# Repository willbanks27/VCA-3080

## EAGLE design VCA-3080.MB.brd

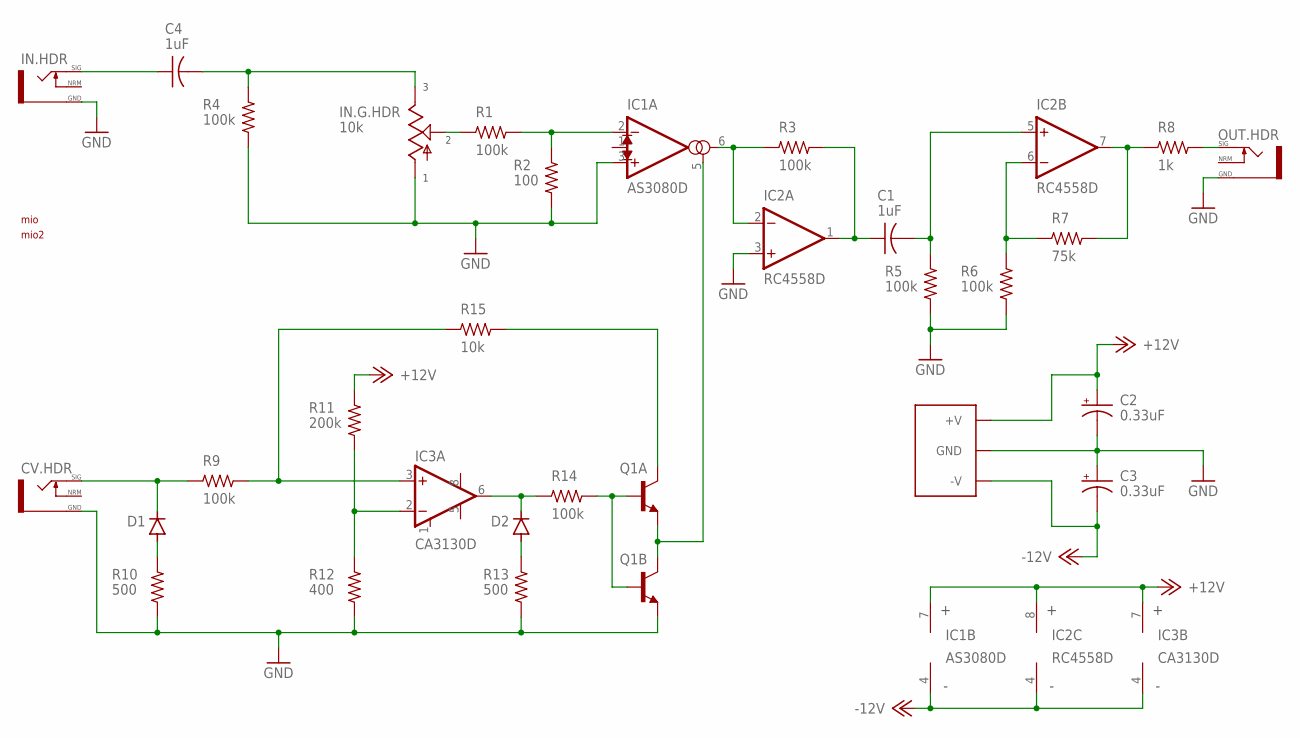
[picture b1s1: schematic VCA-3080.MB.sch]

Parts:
C1, C4: 1uF; C05
C2, C3: 0.33uF; E025
CV.HDR: MONOHDR; HEADER
D1, D2: D-123; SOD-123
IC1: AS3080D; DIL08
IC2: RC4558D; DIL08
IC3: CA3130D; DIL08
IN.G.HDR: 10k; HEADER
IN.HDR: MONOHDR; HEADER
OUT.HDR: MONOHDR; HEADER
Q1: BCM847DS; SOT-23-6
R1, R3, R4, R5, R6, R9, R14: 100k; R1206
R2: 100; R1206
R7: 75k; R1206
R8: 1k; R1206
R10, R13: 500; R1206
R11: 200k; R1206
R12: 400; R1206
R15: 10k; R1206
U$1: 10PIN-PWR; 10PIN-HEADER
U$2: MIO
U$3: MIO2

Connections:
+12V: C2.+, IC1.7 (V+), IC2.8 (V+), IC3.7 (V+), R11.2, U$1.9 (+V), U$1.10 (+V)
-12V: C3.-, IC1.4 (V-), IC2.4 (V-), IC3.4 (V-), U$1.1 (-V), U$1.2 (-V)
GND: C2.-, C3.+, CV.HDR.GND (SLEEVE-GND), IC1.3 (NON-INVERTING(+)), IC2.3 (NON-INVERTING(+)), IN.G.HDR.1, IN.HDR.GND (SLEEVE-GND), OUT.HDR.GND (SLEEVE-GND), Q1.4 (E), R2.1, R4.1, R5.1, R6.1, R10.1, R12.1, R13.1, U$1.3 (GND), U$1.4 (GND), U$1.5 (GND), U$1.6 (GND), U$1.7 (GND), U$1.8 (GND)
unnamed: C4.1, IN.HDR.TIP-SIG
unnamed: IC1.2 (INVERTING(-)), R1.2, R2.2
unnamed: C1.1, IC2.1 (OUT), R3.2
unnamed: IC1.6 (OUT), IC2.2 (INVERTING(-)), R3.1
unnamed: IN.G.HDR.2, R1.1
unnamed: C1.2, IC2.5 (NON-INVERTING(+)), R5.2
unnamed: IC2.6 (INVERTING(-)), R6.2, R7.1
unnamed: IC2.7 (OUT), R7.2, R8.1
unnamed: OUT.HDR.TIP-SIG, R8.2
unnamed: CV.HDR.TIP-SIG, D1.C, R9.1
unnamed: IC3.3 (NON-INVERTING(+)), R9.2, R15.1
unnamed: D1.A, R10.2
unnamed: IC3.2 (INVERTINGA(-)), R11.1, R12.2
unnamed: D2.C, IC3.6 (OUT), R14.1
unnamed: D2.A, R13.2
unnamed: Q1.2 (B), Q1.5 (B), R14.2
unnamed: IC1.5 (I-BIAS), Q1.1 (E), Q1.3 (C)
unnamed: Q1.6 (C), R15.2
unnamed: C4.2, IN.G.HDR.3, R4.2

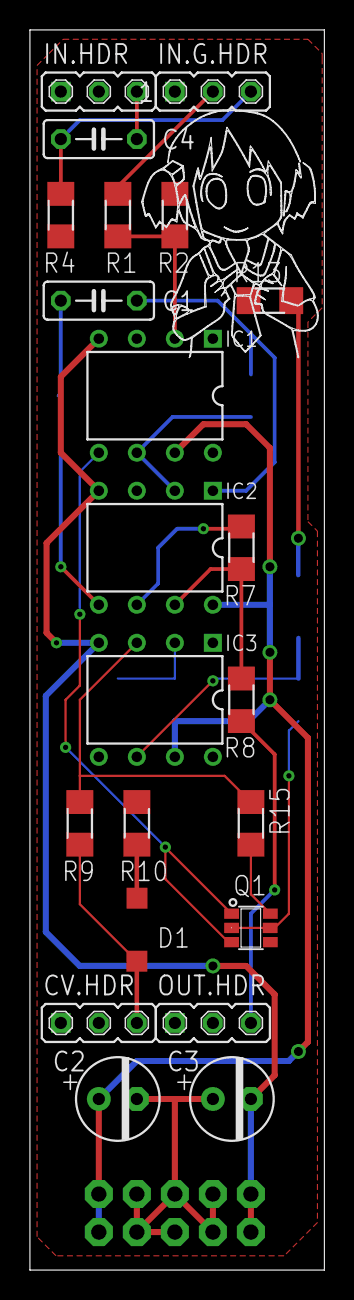
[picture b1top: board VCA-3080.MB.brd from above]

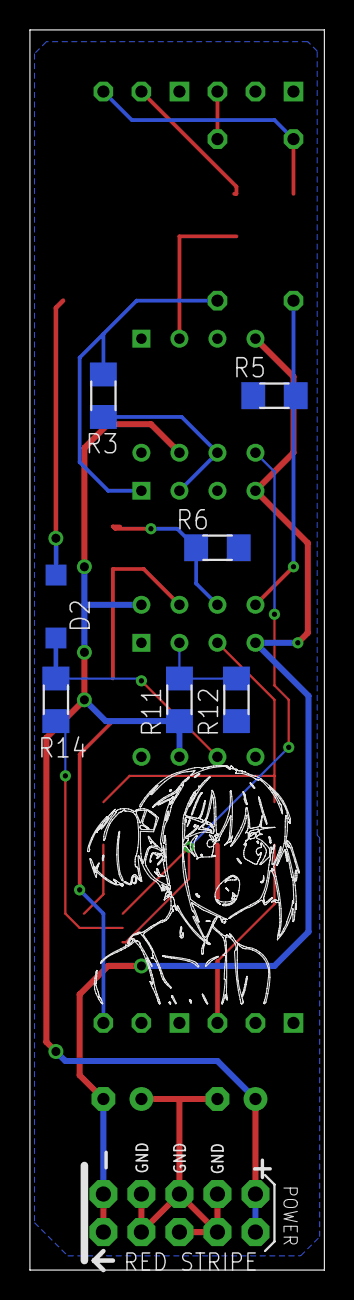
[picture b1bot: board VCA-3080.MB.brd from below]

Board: 2 copper layers, 19.7 x 82.9 mm, 32 parts (9 on the bottom side), 22 nets.

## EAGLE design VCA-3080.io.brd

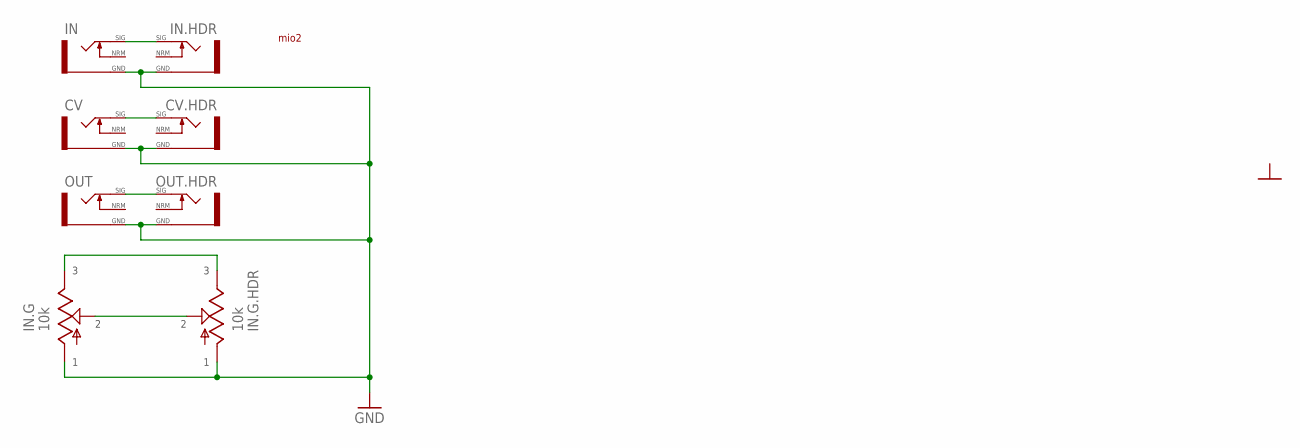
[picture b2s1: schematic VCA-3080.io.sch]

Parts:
CV: MONO301M; PJ301M
CV.HDR: MONOHDR; HEADER
IN: MONO301M; PJ301M
IN.G: 10k; ALPHA-VERT
IN.G.HDR: 10k; HEADER
IN.HDR: MONOHDR; HEADER
OUT: MONO301M; PJ301M
OUT.HDR: MONOHDR; HEADER
U$2: MIO2

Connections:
GND: CV.SLV (SLEEVE-GND), CV.HDR.GND (SLEEVE-GND), IN.SLV (SLEEVE-GND), IN.G.1, IN.G.HDR.1, IN.HDR.GND (SLEEVE-GND), OUT.SLV (SLEEVE-GND), OUT.HDR.GND (SLEEVE-GND)
unnamed: IN.G.3, IN.G.HDR.3
unnamed: IN.G.2, IN.G.HDR.2
unnamed: CV.TIP (TIP-SIG), CV.HDR.TIP-SIG
unnamed: OUT.TIP (TIP-SIG), OUT.HDR.TIP-SIG
unnamed: IN.TIP (TIP-SIG), IN.HDR.TIP-SIG

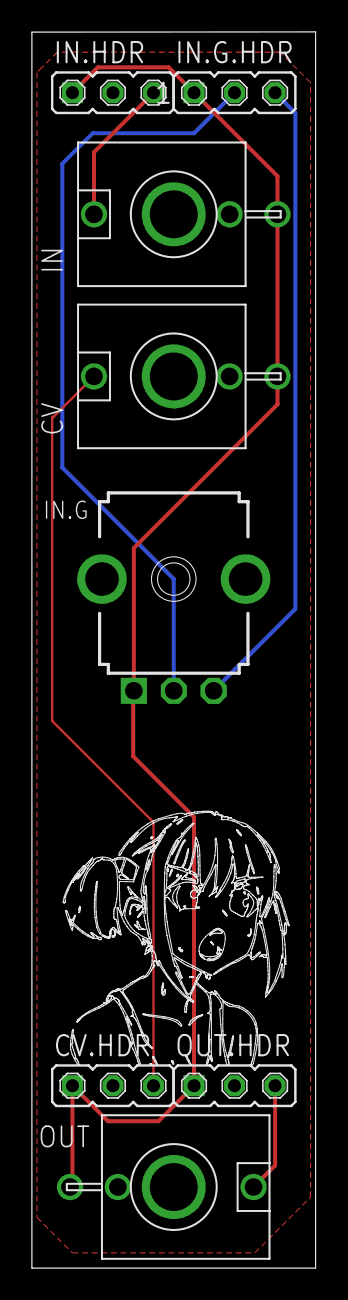
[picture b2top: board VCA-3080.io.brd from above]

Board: 2 copper layers, 17.8 x 77.5 mm, 9 parts (0 on the bottom side), 6 nets.

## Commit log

2023-08-01 Add files via upload
    switched to a stack board design
